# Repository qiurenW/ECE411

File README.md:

# ECE411
A new place to discuss and upload works

This project will develop a temperature controlled fan with Arduino.

The final PCB version is v2.1.

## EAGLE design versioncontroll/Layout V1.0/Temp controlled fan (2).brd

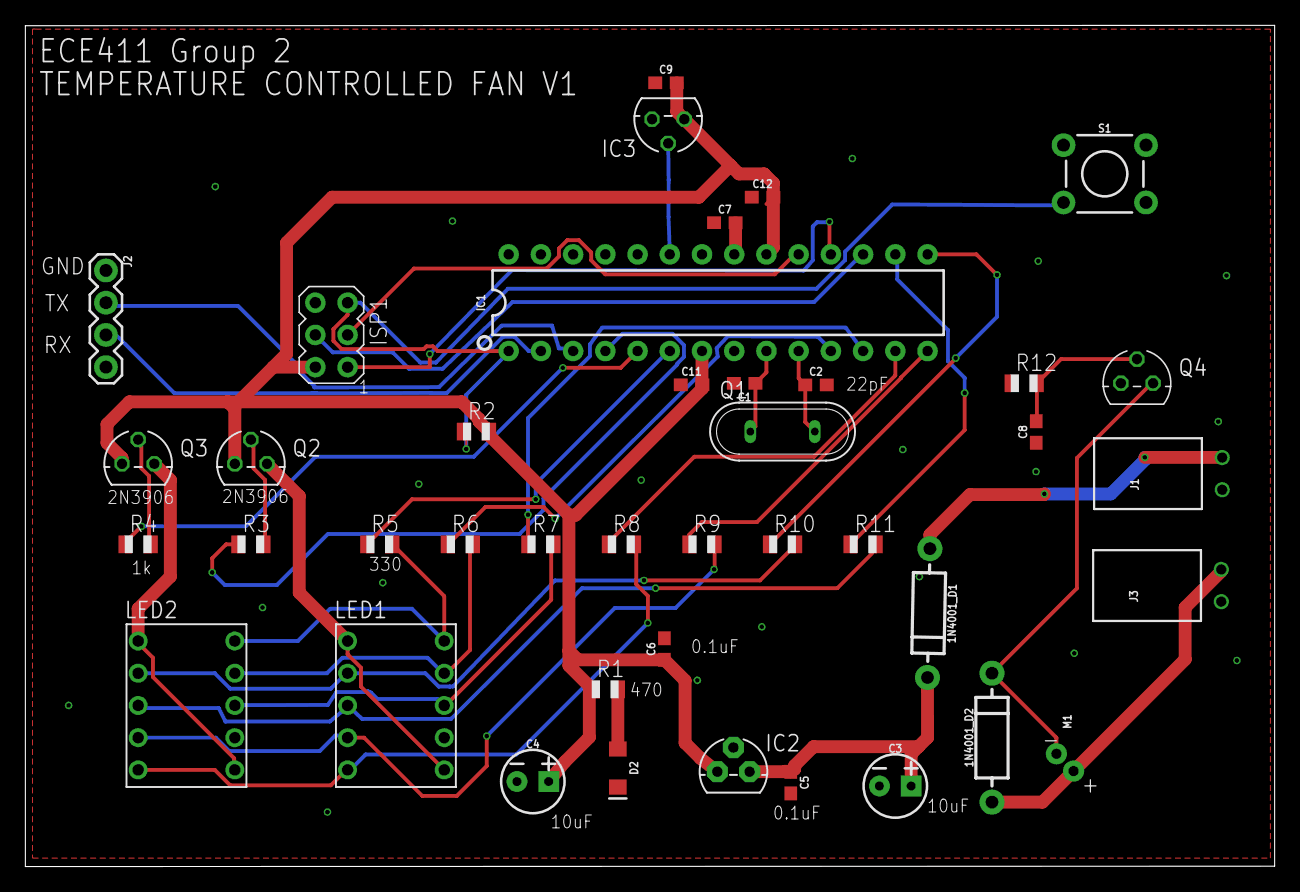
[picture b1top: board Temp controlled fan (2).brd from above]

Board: 2 copper layers, 98.5 x 66.3 mm, 41 parts (0 on the bottom side), 38 nets.

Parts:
1N4001_D1, 1N4001_D2: 1A/50V/1.1V; DIODE-1N4001
C1, C2: 22pF; 0603
C3, C4: 10uF; CPOL-RADIAL-2.5MM-5MM
C5, C6: 0.1uF; 0603
C7, C8, C9, C11, C12: 100nF; 0603
D2: 2.5V; LED-1206
IC1: ATMEGA328P; DIP28
IC2: 7805L; TO92
IC3: LM35; TO92
ISP1: AVRISP-6; AVRISP
J1, J3: 9V/12V; 1X02_RA_PTH_FEMALE
J2: 1X04
LED1, LED2: LA-401MD; LA-401
M1: MOTOR10MM; VIBE-MOTOR-10MM
Q1: 16MHz; QS
Q2, Q3: 2N3906; TO92
Q4: 2N3904; TO92
R1: 470; R0805
R2: 10K; R0805
R3, R4, R12: 1K; R0805
R5, R6, R7, R8, R9, R10, R11: 330; R0805
S1: MOMENTARY-SWITCH-SPST-PTH-6.0MM; TACTILE_SWITCH_PTH_6.0MM

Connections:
CTRL1: IC1.4, R3.1
CTRL2: IC1.5, R4.1
GND: C1.2, C2.2, C3.2, C4.2, C5.2, C6.2, C7.1, C8.1, C9.1, C11.1, C12.1, D2.C, IC1.8, IC1.22, IC2.2, IC3.3, ISP1.6, J1.2, J2.1, J3.2, Q4.3, S1.1
MISO: IC1.18, ISP1.1
MOSI: IC1.17, ISP1.4, R12.1
unnamed: C2.1, IC1.10, Q1.2
unnamed: C7.2, IC1.21
unnamed: C1.1, IC1.9, Q1.1
unnamed: IC1.23, IC3.2
unnamed: D2.A, R1.2
unnamed: 1N4001_D1.C, C3.1, C5.1, IC2.3
unnamed: LED2.1, LED2.6, Q3.1
unnamed: LED1.1, LED1.6, Q2.1
unnamed: Q3.2, R4.2
unnamed: Q2.2, R3.2
unnamed: C8.2, Q4.2, R12.2
unnamed: 1N4001_D2.C, M1.-, Q4.1
unnamed: IC1.16, R11.1
unnamed: IC1.15, R10.1
unnamed: IC1.14, R9.1
unnamed: IC1.13, R8.1
unnamed: IC1.12, R7.1
unnamed: IC1.11, R6.1
unnamed: IC1.6, R5.1
RST: IC1.1, ISP1.5, R2.1, S1.3
RX: IC1.2, J2.3
SCK: IC1.19, ISP1.3
SEG_A: LED1.10, LED2.10, R5.2
SEG_B: LED1.9, LED2.9, R6.2
SEG_C: LED1.8, LED2.8, R7.2
SEG_D: LED1.5, LED2.5, R8.2
SEG_E: LED1.4, LED2.4, R9.2
SEG_F: LED1.2, LED2.2, R10.2
SEG_G: LED1.3, LED2.3, R11.2
TX: IC1.3, J2.2
VCC: C4.1, C6.1, C9.2, C11.2, C12.2, IC1.7, IC1.20, IC2.1, IC3.1, ISP1.2, Q2.3, Q3.3, R1.1, R2.2
V_IN: 1N4001_D1.A, J1.1
V_MOTOR: 1N4001_D2.A, J3.1, M1.+

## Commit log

2017-12-06 Create Arduino Code
2017-12-06 Create schematic
2017-12-06 Update schematic
2017-12-06 Project Schedule V0.1
2017-12-06 Create Total Cost
2017-12-06 Bill Photos
2017-12-07 Project Schedule V0.2
    MS project version
2017-12-07 Create Schematic V2
2017-12-07 Create Version Controll
2017-12-07 TCF v0.1
2017-12-07 Schmatic v2.0
2017-12-07 Create layout
2017-12-07 Layout v1.0
2017-12-07 Schematic v 2.1
2017-12-07 Layout V2.1
    This is the version that we sent it to manufactory.
2017-12-07 Schematic V1 with L293D
2017-12-07 Project PDS
2017-12-07 Homework 3 Decision Making
2017-12-07 Create Test plan blank
2017-12-07 Test Plan Blank
2017-12-07 Create Online Library
2017-12-07 Create PDS
2017-12-07 Update PDS
2017-12-07 Create Project Code
2017-12-07 Create Function
2017-12-07 Create Homework 3
2017-12-07 Create Must Should Bonus
2017-12-07 Create code
2017-12-07 Create Code Version Control
2017-12-07 Rename Code Version Controll/code v1.1 to Code Version Control/code v1.1
2017-12-07 Rename Code Version Controll/README to Code Version Control/README
2017-12-07 Rename Code Version Controll/code v1.2 to Code Version Control/code v1.2
2017-12-07 Rename Code Version Controll/code v1.3 to Code Version Control/code v1.3
2017-12-07 Rename Code Version Controll/Code v1.0/code to Code Version Control/code v0.1 prototype
2017-12-07 Rename Layout v0.1 to README
2017-12-08 Final Presentation of ECE411

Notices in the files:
parts and their libraries:
SparkFun-DiscreteSemi: Licensing: Creative Commons ShareAlike 4.0 International - https://creativecommons.org/licenses/by-sa/4.0
